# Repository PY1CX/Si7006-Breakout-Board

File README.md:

# Si7006-Breakout-Board
This is a little Breakout board that I made to test the Si7006 instead of using a franksteinlike p2p mount.

R1 and R2 are I2C pull-up resistors in a 0805 package, 10kohm is ok.
C1 is a little 100nF 0805 package capacitor, use whatever that you have on your junkbox.

I want to thanks DIYmodules.org for supplying the Eagle Library.

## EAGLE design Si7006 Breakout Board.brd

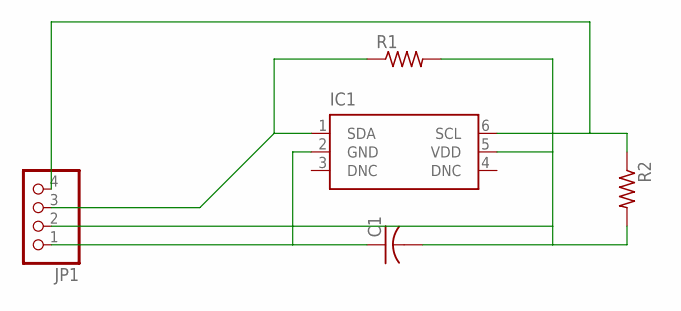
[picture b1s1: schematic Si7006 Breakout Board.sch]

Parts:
C1: C-USC0805; C0805
IC1: SI7006-A10-IM; DFN6-3X3
JP1: PINHD-1X4; 1X04
R1, R2: R-US_R0805; R0805

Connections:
unnamed: C1.1, IC1.2 (GND), JP1.1
unnamed: C1.2, IC1.5 (VDD), JP1.2, R1.2, R2.2
unnamed: IC1.1 (SDA), JP1.3, R1.1
unnamed: IC1.6 (SCL), JP1.4, R2.1

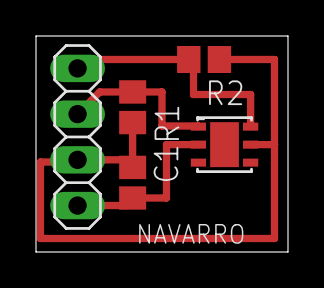
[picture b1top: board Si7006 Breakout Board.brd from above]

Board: 2 copper layers, 14.0 x 12.0 mm, 5 parts (0 on the bottom side), 4 nets.

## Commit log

2015-11-27 First commit of the Si7006 Breakout board.
2015-11-27 Revised the README session and added thanks for the DIYModules supplying the Library and added general info on the resistors and capacitors that you should use.

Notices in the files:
parts and their libraries:
si70xx-10: (c) 2014 Samuel Lourenço
